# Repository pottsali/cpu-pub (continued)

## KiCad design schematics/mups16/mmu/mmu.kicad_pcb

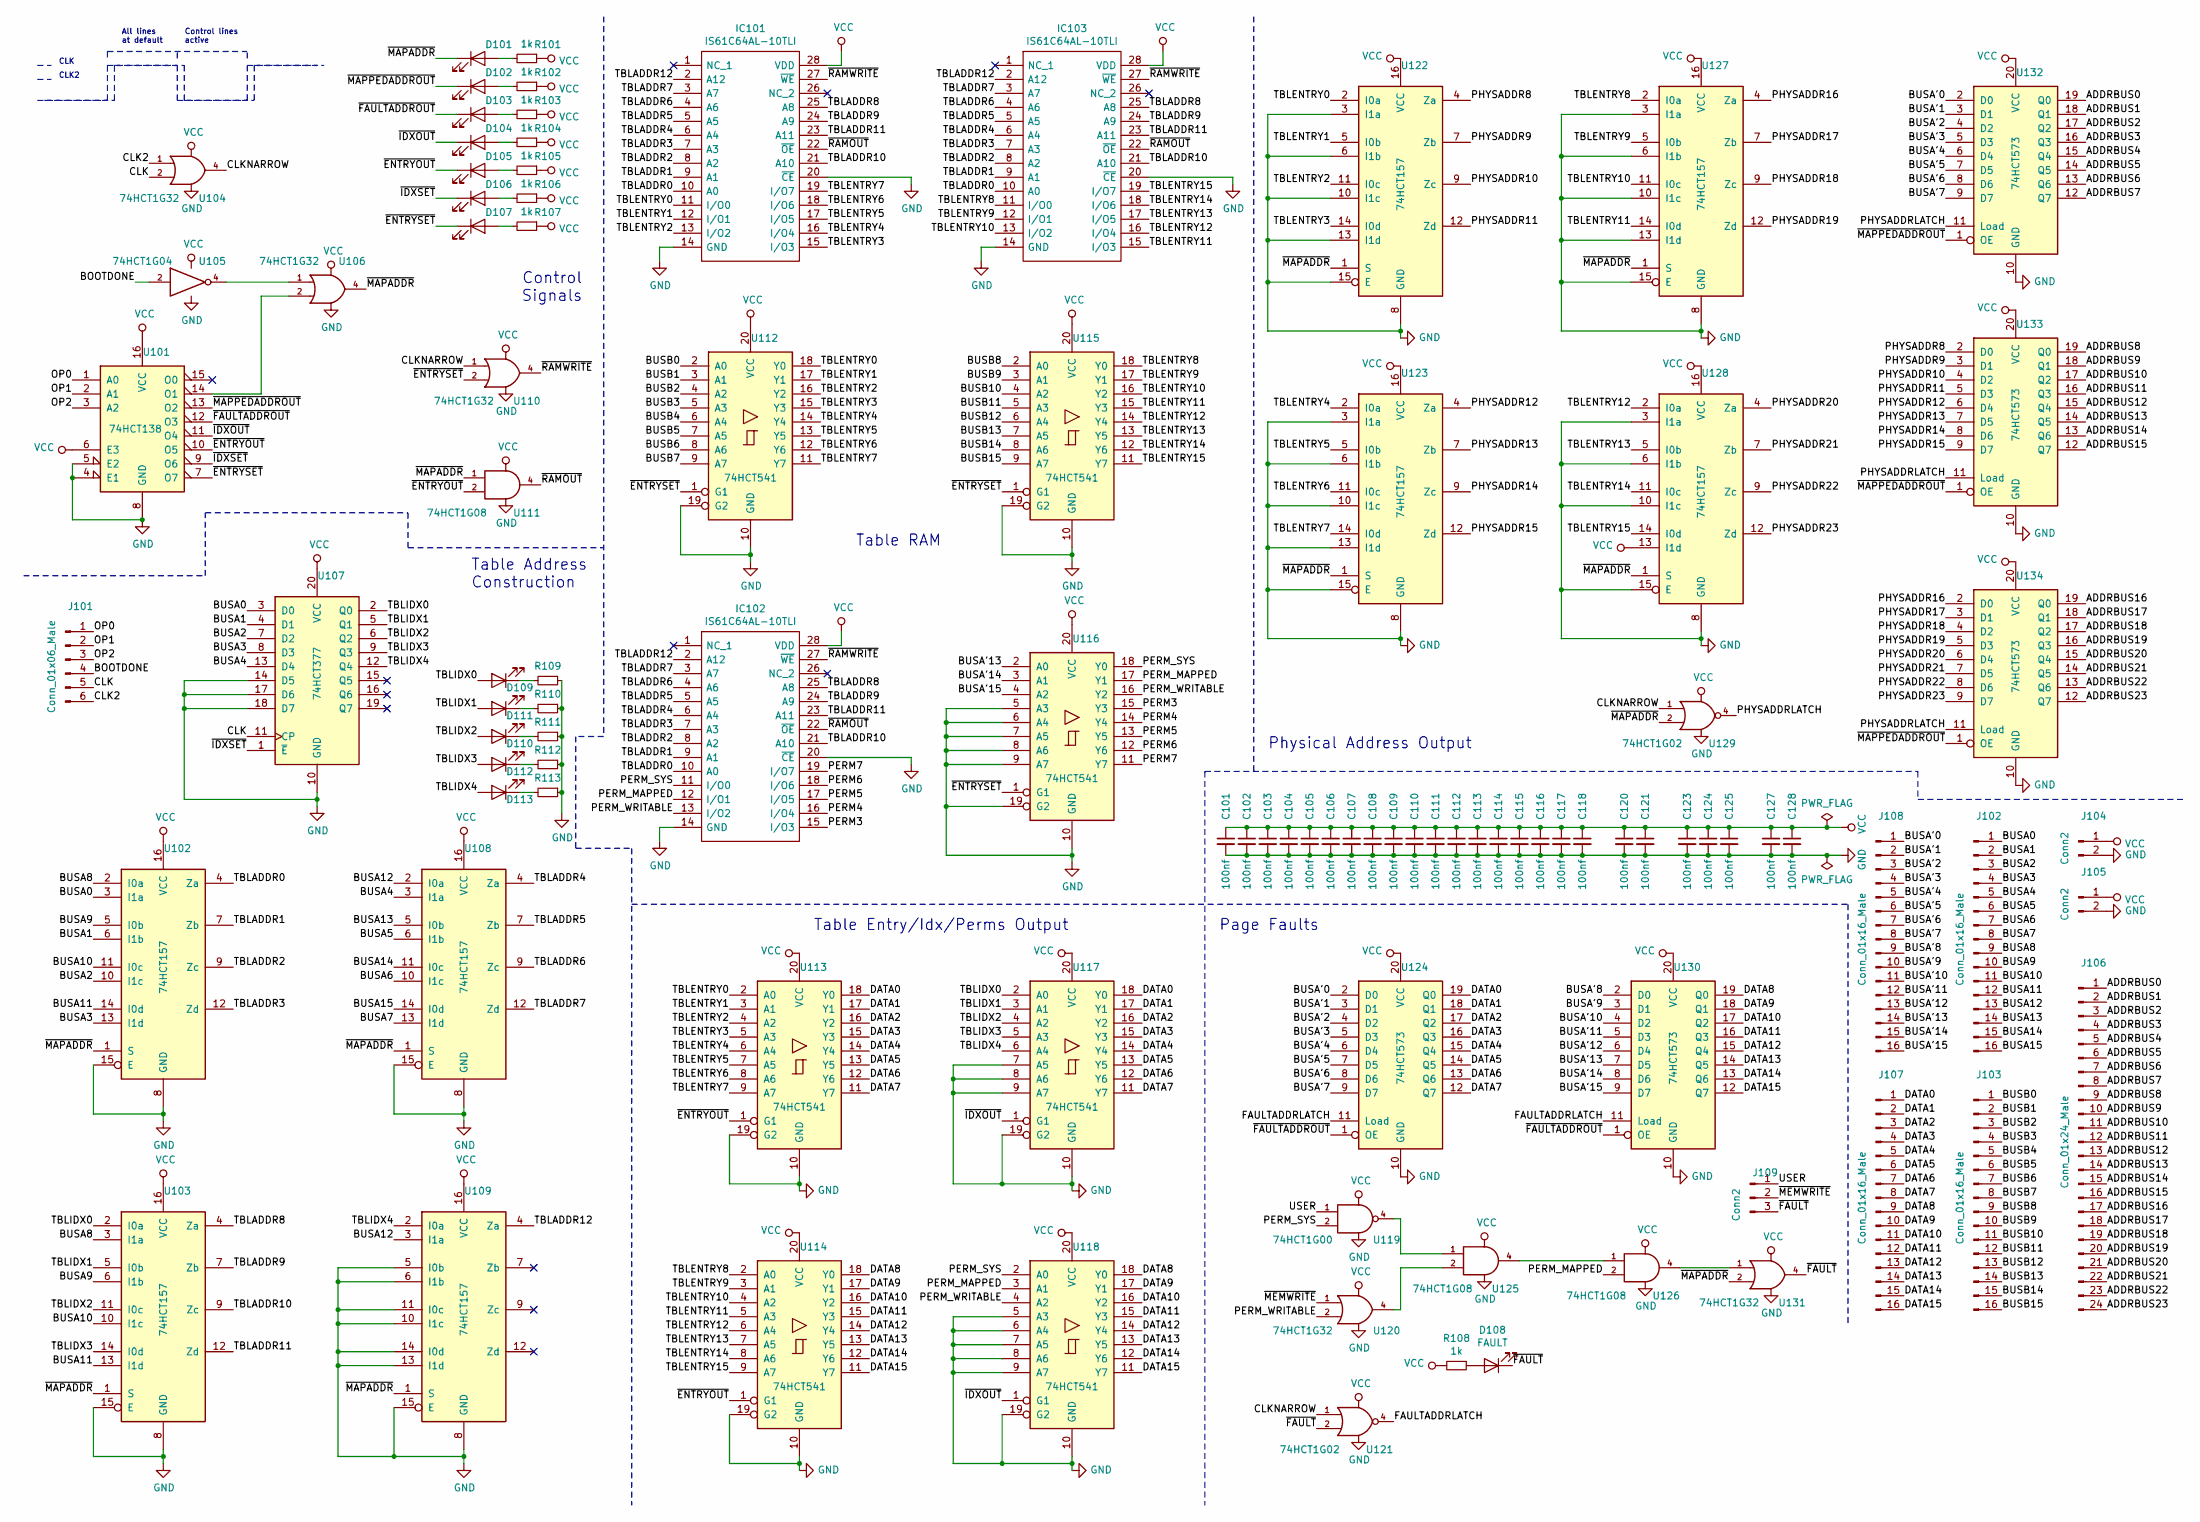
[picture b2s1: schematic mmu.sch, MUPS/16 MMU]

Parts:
C101, C102, C103, C104, C105, C106, C107, C108, C109, C110, C111, C112, C113, C114, C115, C116, C117, C118, C120, C121, C123, C124, C125, C127, C128: 100nf; C_0805_2012Metric
D101: Map Addr; LED_0805_2012Metric
D102: PAddr Out; LED_0805_2012Metric
D103: FAddr Out; LED_0805_2012Metric
D104: TI/P Out; LED_0805_2012Metric
D105: TE Out; LED_0805_2012Metric
D106: TI Set; LED_0805_2012Metric
D107: TE Set; LED_0805_2012Metric
D108: FAULT; LED_0805_2012Metric
D109, D110, D111, D112, D113: LED; LED_0805_2012Metric
IC101, IC102, IC103: IS61C64AL-10TLI; SOP55P1340X120-28N; Mouser Part Number 870-IS61C64AL-10TLI
J101: Conn_01x06_Male; PinHeader_1x06_P2.54mm_Vertical
J102, J103, J107, J108: Conn_01x16_Male; PinHeader_1x16_P2.54mm_Vertical
J104, J105: Conn2; PinHeader_1x02_P2.54mm_Vertical
J106: Conn_01x24_Male; PinHeader_1x24_P2.54mm_Vertical
J109: Conn2; PinHeader_1x03_P2.54mm_Vertical
R101, R102, R103, R104, R105, R106, R107, R108: 1k; R_0805_2012Metric
R109, R110, R111, R112, R113: R_Small; R_0805_2012Metric
U101: 74HCT138; SOIC-16_3.9x9.9mm_P1.27mm
U102, U103, U108, U109, U122, U123, U127, U128: 74HCT157; SOIC-16_3.9x9.9mm_P1.27mm
U104, U106, U110, U120, U131: 74HCT1G32; TSOP-5_1.65x3.05mm_P0.95mm
U105: 74HCT1G04; TSOP-5_1.65x3.05mm_P0.95mm
U107: 74HCT377; SO-20_12.8x7.5mm_P1.27mm
U111, U125, U126: 74HCT1G08; TSOP-5_1.65x3.05mm_P0.95mm
U112, U113, U114, U115, U116, U117, U118: 74HCT541; SOIC-20W_7.5x12.8mm_P1.27mm
U119: 74HCT1G00; TSOP-5_1.65x3.05mm_P0.95mm
U121, U129: 74HCT1G02; SOT65P212X110-5N
U124, U130, U132, U133, U134: 74HCT573; SO-20_12.8x7.5mm_P1.27mm

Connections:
/ADDRBUS0: J106.1, U132.19 (Q0)
/ADDRBUS1: J106.2, U132.18 (Q1)
/ADDRBUS2: J106.3, U132.17 (Q2)
/ADDRBUS3: J106.4, U132.16 (Q3)
/ADDRBUS4: J106.5, U132.15 (Q4)
/ADDRBUS5: J106.6, U132.14 (Q5)
/ADDRBUS6: J106.7, U132.13 (Q6)
/ADDRBUS7: J106.8, U132.12 (Q7)
/ADDRBUS8: J106.9, U133.19 (Q0)
/ADDRBUS9: J106.10, U133.18 (Q1)
/ADDRBUS10: J106.11, U133.17 (Q2)
/ADDRBUS11: J106.12, U133.16 (Q3)
/ADDRBUS12: J106.13, U133.15 (Q4)
/ADDRBUS13: J106.14, U133.14 (Q5)
/ADDRBUS14: J106.15, U133.13 (Q6)
/ADDRBUS15: J106.16, U133.12 (Q7)
/ADDRBUS16: J106.17, U134.19 (Q0)
/ADDRBUS17: J106.18, U134.18 (Q1)
/ADDRBUS18: J106.19, U134.17 (Q2)
/ADDRBUS19: J106.20, U134.16 (Q3)
/ADDRBUS20: J106.21, U134.15 (Q4)
/ADDRBUS21: J106.22, U134.14 (Q5)
/ADDRBUS22: J106.23, U134.13 (Q6)
/ADDRBUS23: J106.24, U134.12 (Q7)
/BOOTDONE: J101.4, U105.2
/BUSA0: J102.1, U102.3 (I1a), U107.3 (D0)
/BUSA1: J102.2, U102.6 (I1b), U107.4 (D1)
/BUSA2: J102.3, U102.10 (I1c), U107.7 (D2)
/BUSA3: J102.4, U102.13 (I1d), U107.8 (D3)
/BUSA4: J102.5, U107.13 (D4), U108.3 (I1a)
/BUSA5: J102.6, U108.6 (I1b)
/BUSA6: J102.7, U108.10 (I1c)
/BUSA7: J102.8, U108.13 (I1d)
/BUSA8: J102.9, U102.2 (I0a), U103.3 (I1a)
/BUSA9: J102.10, U102.5 (I0b), U103.6 (I1b)
/BUSA10: J102.11, U102.11 (I0c), U103.10 (I1c)
/BUSA11: J102.12, U102.14 (I0d), U103.13 (I1d)
/BUSA12: J102.13, U108.2 (I0a), U109.3 (I1a)
/BUSA13: J102.14, U108.5 (I0b)
/BUSA14: J102.15, U108.11 (I0c)
/BUSA15: J102.16, U108.14 (I0d)
/BUSA'0: J108.1, U124.2 (D0), U132.2 (D0)
/BUSA'1: J108.2, U124.3 (D1), U132.3 (D1)
/BUSA'2: J108.3, U124.4 (D2), U132.4 (D2)
/BUSA'3: J108.4, U124.5 (D3), U132.5 (D3)
/BUSA'4: J108.5, U124.6 (D4), U132.6 (D4)
/BUSA'5: J108.6, U124.7 (D5), U132.7 (D5)
/BUSA'6: J108.7, U124.8 (D6), U132.8 (D6)
/BUSA'7: J108.8, U124.9 (D7), U132.9 (D7)
/BUSA'8: J108.9, U130.2 (D0)
/BUSA'9: J108.10, U130.3 (D1)
/BUSA'10: J108.11, U130.4 (D2)
/BUSA'11: J108.12, U130.5 (D3)
/BUSA'12: J108.13, U130.6 (D4)
/BUSA'13: J108.14, U116.2 (A0), U130.7 (D5)
/BUSA'14: J108.15, U116.3 (A1), U130.8 (D6)
/BUSA'15: J108.16, U116.4 (A2), U130.9 (D7)
/BUSB0: J103.1, U112.2 (A0)
/BUSB1: J103.2, U112.3 (A1)
/BUSB2: J103.3, U112.4 (A2)
/BUSB3: J103.4, U112.5 (A3)
/BUSB4: J103.5, U112.6 (A4)
/BUSB5: J103.6, U112.7 (A5)
/BUSB6: J103.7, U112.8 (A6)
/BUSB7: J103.8, U112.9 (A7)
/BUSB8: J103.9, U115.2 (A0)
/BUSB9: J103.10, U115.3 (A1)
/BUSB10: J103.11, U115.4 (A2)
/BUSB11: J103.12, U115.5 (A3)
/BUSB12: J103.13, U115.6 (A4)
/BUSB13: J103.14, U115.7 (A5)
/BUSB14: J103.15, U115.8 (A6)
/BUSB15: J103.16, U115.9 (A7)
/CLK: J101.5, U104.2, U107.11 (CP)
/CLK2: J101.6, U104.1
/CLKNARROW: U104.4, U110.1, U121.1, U129.1
/DATA0: J107.1, U113.18 (Y0), U117.18 (Y0), U124.19 (Q0)
/DATA1: J107.2, U113.17 (Y1), U117.17 (Y1), U124.18 (Q1)
/DATA2: J107.3, U113.16 (Y2), U117.16 (Y2), U124.17 (Q2)
/DATA3: J107.4, U113.15 (Y3), U117.15 (Y3), U124.16 (Q3)
/DATA4: J107.5, U113.14 (Y4), U117.14 (Y4), U124.15 (Q4)
/DATA5: J107.6, U113.13 (Y5), U117.13 (Y5), U124.14 (Q5)
/DATA6: J107.7, U113.12 (Y6), U117.12 (Y6), U124.13 (Q6)
/DATA7: J107.8, U113.11 (Y7), U117.11 (Y7), U124.12 (Q7)
/DATA8: J107.9, U114.18 (Y0), U118.18 (Y0), U130.19 (Q0)
/DATA9: J107.10, U114.17 (Y1), U118.17 (Y1), U130.18 (Q1)
/DATA10: J107.11, U114.16 (Y2), U118.16 (Y2), U130.17 (Q2)
/DATA11: J107.12, U114.15 (Y3), U118.15 (Y3), U130.16 (Q3)
/DATA12: J107.13, U114.14 (Y4), U118.14 (Y4), U130.15 (Q4)
/DATA13: J107.14, U114.13 (Y5), U118.13 (Y5), U130.14 (Q5)
/DATA14: J107.15, U114.12 (Y6), U118.12 (Y6), U130.13 (Q6)
/DATA15: J107.16, U114.11 (Y7), U118.11 (Y7), U130.12 (Q7)
/FAULTADDRLATCH: U121.4, U124.11 (Load), U130.11 (Load)
/OP0: J101.1, U101.1 (A0)
/OP1: J101.2, U101.2 (A1)
/OP2: J101.3, U101.3 (A2)
/PERM3: IC102.15 (I/O3), U116.15 (Y3)
/PERM4: IC102.16 (I/O4), U116.14 (Y4)
/PERM5: IC102.17 (I/O5), U116.13 (Y5)
/PERM6: IC102.18 (I/O6), U116.12 (Y6)
/PERM7: IC102.19 (I/O7), U116.11 (Y7)
/PERM_MAPPED: IC102.12 (I/O1), U116.17 (Y1), U118.3 (A1), U126.2
/PERM_SYS: IC102.11 (I/O0), U116.18 (Y0), U118.2 (A0), U119.2
/PERM_WRITABLE: IC102.13 (I/O2), U116.16 (Y2), U118.4 (A2), U120.2
/PHYSADDR8: U122.4 (Za), U133.2 (D0)
/PHYSADDR9: U122.7 (Zb), U133.3 (D1)
/PHYSADDR10: U122.9 (Zc), U133.4 (D2)
/PHYSADDR11: U122.12 (Zd), U133.5 (D3)
/PHYSADDR12: U123.4 (Za), U133.6 (D4)
/PHYSADDR13: U123.7 (Zb), U133.7 (D5)
/PHYSADDR14: U123.9 (Zc), U133.8 (D6)
/PHYSADDR15: U123.12 (Zd), U133.9 (D7)
/PHYSADDR16: U127.4 (Za), U134.2 (D0)
/PHYSADDR17: U127.7 (Zb), U134.3 (D1)
/PHYSADDR18: U127.9 (Zc), U134.4 (D2)
/PHYSADDR19: U127.12 (Zd), U134.5 (D3)
/PHYSADDR20: U128.4 (Za), U134.6 (D4)
/PHYSADDR21: U128.7 (Zb), U134.7 (D5)
/PHYSADDR22: U128.9 (Zc), U134.8 (D6)
/PHYSADDR23: U128.12 (Zd), U134.9 (D7)
/PHYSADDRLATCH: U129.4, U132.11 (Load), U133.11 (Load), U134.11 (Load)
/TBLADDR0: IC101.10 (A0), IC102.10 (A0), IC103.10 (A0), U102.4 (Za)
/TBLADDR1: IC101.9 (A1), IC102.9 (A1), IC103.9 (A1), U102.7 (Zb)
/TBLADDR2: IC101.8 (A2), IC102.8 (A2), IC103.8 (A2), U102.9 (Zc)
/TBLADDR3: IC101.7 (A3), IC102.7 (A3), IC103.7 (A3), U102.12 (Zd)
/TBLADDR4: IC101.6 (A4), IC102.6 (A4), IC103.6 (A4), U108.4 (Za)
/TBLADDR5: IC101.5 (A5), IC102.5 (A5), IC103.5 (A5), U108.7 (Zb)
/TBLADDR6: IC101.4 (A6), IC102.4 (A6), IC103.4 (A6), U108.9 (Zc)
/TBLADDR7: IC101.3 (A7), IC102.3 (A7), IC103.3 (A7), U108.12 (Zd)
/TBLADDR8: IC101.25 (A8), IC102.25 (A8), IC103.25 (A8), U103.4 (Za)
/TBLADDR9: IC101.24 (A9), IC102.24 (A9), IC103.24 (A9), U103.7 (Zb)
/TBLADDR10: IC101.21 (A10), IC102.21 (A10), IC103.21 (A10), U103.9 (Zc)
/TBLADDR11: IC101.23 (A11), IC102.23 (A11), IC103.23 (A11), U103.12 (Zd)
/TBLADDR12: IC101.2 (A12), IC102.2 (A12), IC103.2 (A12), U109.4 (Za)
/TBLENTRY0: IC101.11 (I/O0), U112.18 (Y0), U113.2 (A0), U122.2 (I0a)
/TBLENTRY1: IC101.12 (I/O1), U112.17 (Y1), U113.3 (A1), U122.5 (I0b)
/TBLENTRY2: IC101.13 (I/O2), U112.16 (Y2), U113.4 (A2), U122.11 (I0c)
/TBLENTRY3: IC101.15 (I/O3), U112.15 (Y3), U113.5 (A3), U122.14 (I0d)
/TBLENTRY4: IC101.16 (I/O4), U112.14 (Y4), U113.6 (A4), U123.2 (I0a)
/TBLENTRY5: IC101.17 (I/O5), U112.13 (Y5), U113.7 (A5), U123.5 (I0b)
/TBLENTRY6: IC101.18 (I/O6), U112.12 (Y6), U113.8 (A6), U123.11 (I0c)
/TBLENTRY7: IC101.19 (I/O7), U112.11 (Y7), U113.9 (A7), U123.14 (I0d)
/TBLENTRY8: IC103.11 (I/O0), U114.2 (A0), U115.18 (Y0), U127.2 (I0a)
/TBLENTRY9: IC103.12 (I/O1), U114.3 (A1), U115.17 (Y1), U127.5 (I0b)
/TBLENTRY10: IC103.13 (I/O2), U114.4 (A2), U115.16 (Y2), U127.11 (I0c)
/TBLENTRY11: IC103.15 (I/O3), U114.5 (A3), U115.15 (Y3), U127.14 (I0d)
/TBLENTRY12: IC103.16 (I/O4), U114.6 (A4), U115.14 (Y4), U128.2 (I0a)
/TBLENTRY13: IC103.17 (I/O5), U114.7 (A5), U115.13 (Y5), U128.5 (I0b)
/TBLENTRY14: IC103.18 (I/O6), U114.8 (A6), U115.12 (Y6), U128.11 (I0c)
/TBLENTRY15: IC103.19 (I/O7), U114.9 (A7), U115.11 (Y7), U128.14 (I0d)
/TBLIDX0: D109.2 (A), U103.2 (I0a), U107.2 (Q0), U117.2 (A0)
/TBLIDX1: D110.2 (A), U103.5 (I0b), U107.5 (Q1), U117.3 (A1)
/TBLIDX2: D111.2 (A), U103.11 (I0c), U107.6 (Q2), U117.4 (A2)
/TBLIDX3: D112.2 (A), U103.14 (I0d), U107.9 (Q3), U117.5 (A3)
/TBLIDX4: D113.2 (A), U107.12 (Q4), U109.2 (I0a), U117.6 (A4)
/USER: J109.1, U119.1
/~ENTRYOUT: D105.1 (K), U101.10 (O5), U111.2, U113.1 (G1), U114.1 (G1)
/~ENTRYSET: D107.1 (K), U101.7 (O7), U110.2, U112.1 (G1), U115.1 (G1), U116.1 (G1)
/~FAULT: D108.1 (K), J109.3, U121.2, U131.4
/~FAULTADDROUT: D103.1 (K), U101.12 (O3), U124.1 (OE), U130.1 (OE)
/~IDXOUT: D104.1 (K), U101.11 (O4), U117.1 (G1), U118.1 (G1)
/~IDXSET: D106.1 (K), U101.9 (O6), U107.1 (~E)
/~MAPADDR: D101.1 (K), U102.1 (S), U103.1 (S), U106.4, U108.1 (S), U109.1 (S), U111.1, U122.1 (S), U123.1 (S), U127.1 (S), U128.1 (S), U129.2, U131.2
/~MAPPEDADDROUT: D102.1 (K), U101.13 (O2), U132.1 (OE), U133.1 (OE), U134.1 (OE)
/~MEMWRITE: J109.2, U120.1
/~RAMOUT: IC101.22 (~OE), IC102.22 (~OE), IC103.22 (~OE), U111.4
/~RAMWRITE: IC101.27 (~WE), IC102.27 (~WE), IC103.27 (~WE), U110.4
GND: C101.2, C102.2, C103.2, C104.2, C105.2, C106.2, C107.2, C108.2, C109.2, C110.2, C111.2, C112.2, C113.2, C114.2, C115.2, C116.2, C117.2, C118.2, C120.2, C121.2, C123.2, C124.2, C125.2, C127.2, C128.2, IC101.14 (GND), IC101.20 (~CE), IC102.14 (GND), IC102.20 (~CE), IC103.14 (GND), IC103.20 (~CE), J104.2, J105.2, R109.1, R110.1, R111.1, R112.1, R113.1, U101.4 (E1), U101.5 (E2), U101.8 (GND), U102.8 (GND), U102.15 (E), U103.8 (GND), U103.15 (E), U104.3 (GND), U105.3 (GND), U106.3 (GND), U107.10 (GND), U107.14 (D5), U107.17 (D6), U107.18 (D7), U108.8 (GND), U108.15 (E), U109.5 (I0b), U109.6 (I1b), U109.8 (GND), U109.10 (I1c), U109.11 (I0c), U109.13 (I1d), U109.14 (I0d), U109.15 (E), U110.3 (GND), U111.3 (GND), U112.10 (GND), U112.19 (G2), U113.10 (GND), U113.19 (G2), U114.10 (GND), U114.19 (G2), U115.10 (GND), U115.19 (G2), U116.5 (A3), U116.6 (A4), U116.7 (A5), U116.8 (A6), U116.9 (A7), U116.10 (GND), U116.19 (G2), U117.7 (A5), U117.8 (A6), U117.9 (A7), U117.10 (GND), U117.19 (G2), U118.5 (A3), U118.6 (A4), U118.7 (A5), U118.8 (A6), U118.9 (A7), U118.10 (GND), U118.19 (G2), U119.3 (GND), U120.3 (GND), U121.3 (GND), U122.3 (I1a), U122.6 (I1b), U122.8 (GND), U122.10 (I1c), U122.13 (I1d), U122.15 (E), U123.3 (I1a), U123.6 (I1b), U123.8 (GND), U123.10 (I1c), U123.13 (I1d), U123.15 (E), U124.10 (GND), U125.3 (GND), U126.3 (GND), U127.3 (I1a), U127.6 (I1b), U127.8 (GND), U127.10 (I1c), U127.13 (I1d), U127.15 (E), U128.3 (I1a), U128.6 (I1b), U128.8 (GND), U128.10 (I1c), U128.15 (E), U129.3 (GND), U130.10 (GND), U131.3 (GND), U132.10 (GND), U133.10 (GND), U134.10 (GND)
unnamed: D101.2 (A), R101.2
unnamed: D102.2 (A), R102.2
unnamed: D103.2 (A), R103.2
unnamed: D104.2 (A), R104.2
unnamed: D105.2 (A), R105.2
unnamed: D106.2 (A), R106.2
unnamed: D107.2 (A), R107.2
unnamed: D108.2 (A), R108.1
unnamed: D109.1 (K), R109.2
unnamed: D110.1 (K), R110.2
unnamed: D111.1 (K), R111.2
unnamed: D112.1 (K), R112.2
unnamed: D113.1 (K), R113.2
unnamed: U101.14 (O1), U106.2
unnamed: U105.4, U106.1
unnamed: U119.4, U125.1
unnamed: U120.4, U125.2
unnamed: U125.4, U126.1
unnamed: U126.4, U131.1
VCC: C101.1, C102.1, C103.1, C104.1, C105.1, C106.1, C107.1, C108.1, C109.1, C110.1, C111.1, C112.1, C113.1, C114.1, C115.1, C116.1, C117.1, C118.1, C120.1, C121.1, C123.1, C124.1, C125.1, C127.1, C128.1, IC101.28 (VDD), IC102.28 (VDD), IC103.28 (VDD), J104.1, J105.1, R101.1, R102.1, R103.1, R104.1, R105.1, R106.1, R107.1, R108.2, U101.6 (E3), U101.16 (VCC), U102.16 (VCC), U103.16 (VCC), U104.5 (VCC), U105.5 (VCC), U106.5 (VCC), U107.20 (VCC), U108.16 (VCC), U109.16 (VCC), U110.5 (VCC), U111.5 (VCC), U112.20 (VCC), U113.20 (VCC), U114.20 (VCC), U115.20 (VCC), U116.20 (VCC), U117.20 (VCC), U118.20 (VCC), U119.5 (VCC), U120.5 (VCC), U121.5 (VCC), U122.16 (VCC), U123.16 (VCC), U124.20 (VCC), U125.5 (VCC), U126.5 (VCC), U127.16 (VCC), U128.13 (I1d), U128.16 (VCC), U129.5 (VCC), U130.20 (VCC), U131.5 (VCC), U132.20 (VCC), U133.20 (VCC), U134.20 (VCC)

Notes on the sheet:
All lines at default
Control lines active
CLK
CLK2
Table Address Construction
Control Signals
Table RAM
Table Entry/Idx/Perms Output
Physical Address Output
Page Faults

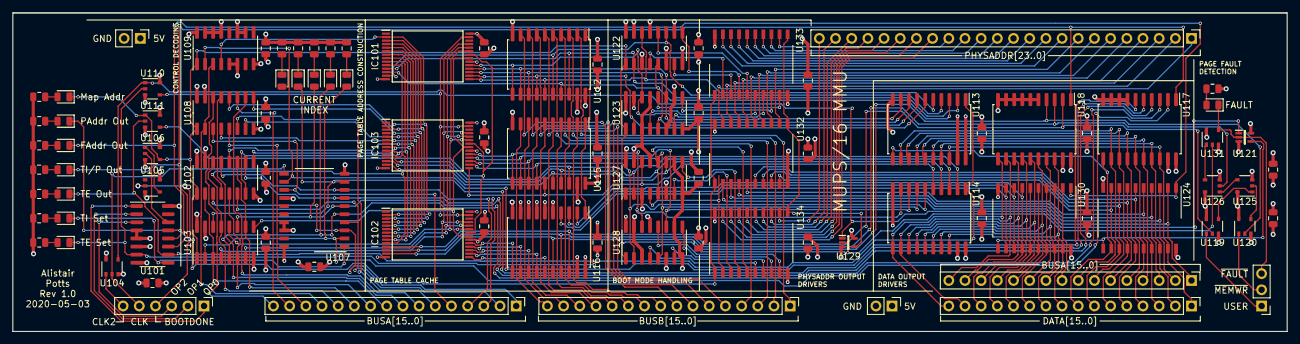
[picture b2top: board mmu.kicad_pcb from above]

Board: 4 copper layers, 200.0 x 50.0 mm, 97 parts (0 on the bottom side), 188 nets.

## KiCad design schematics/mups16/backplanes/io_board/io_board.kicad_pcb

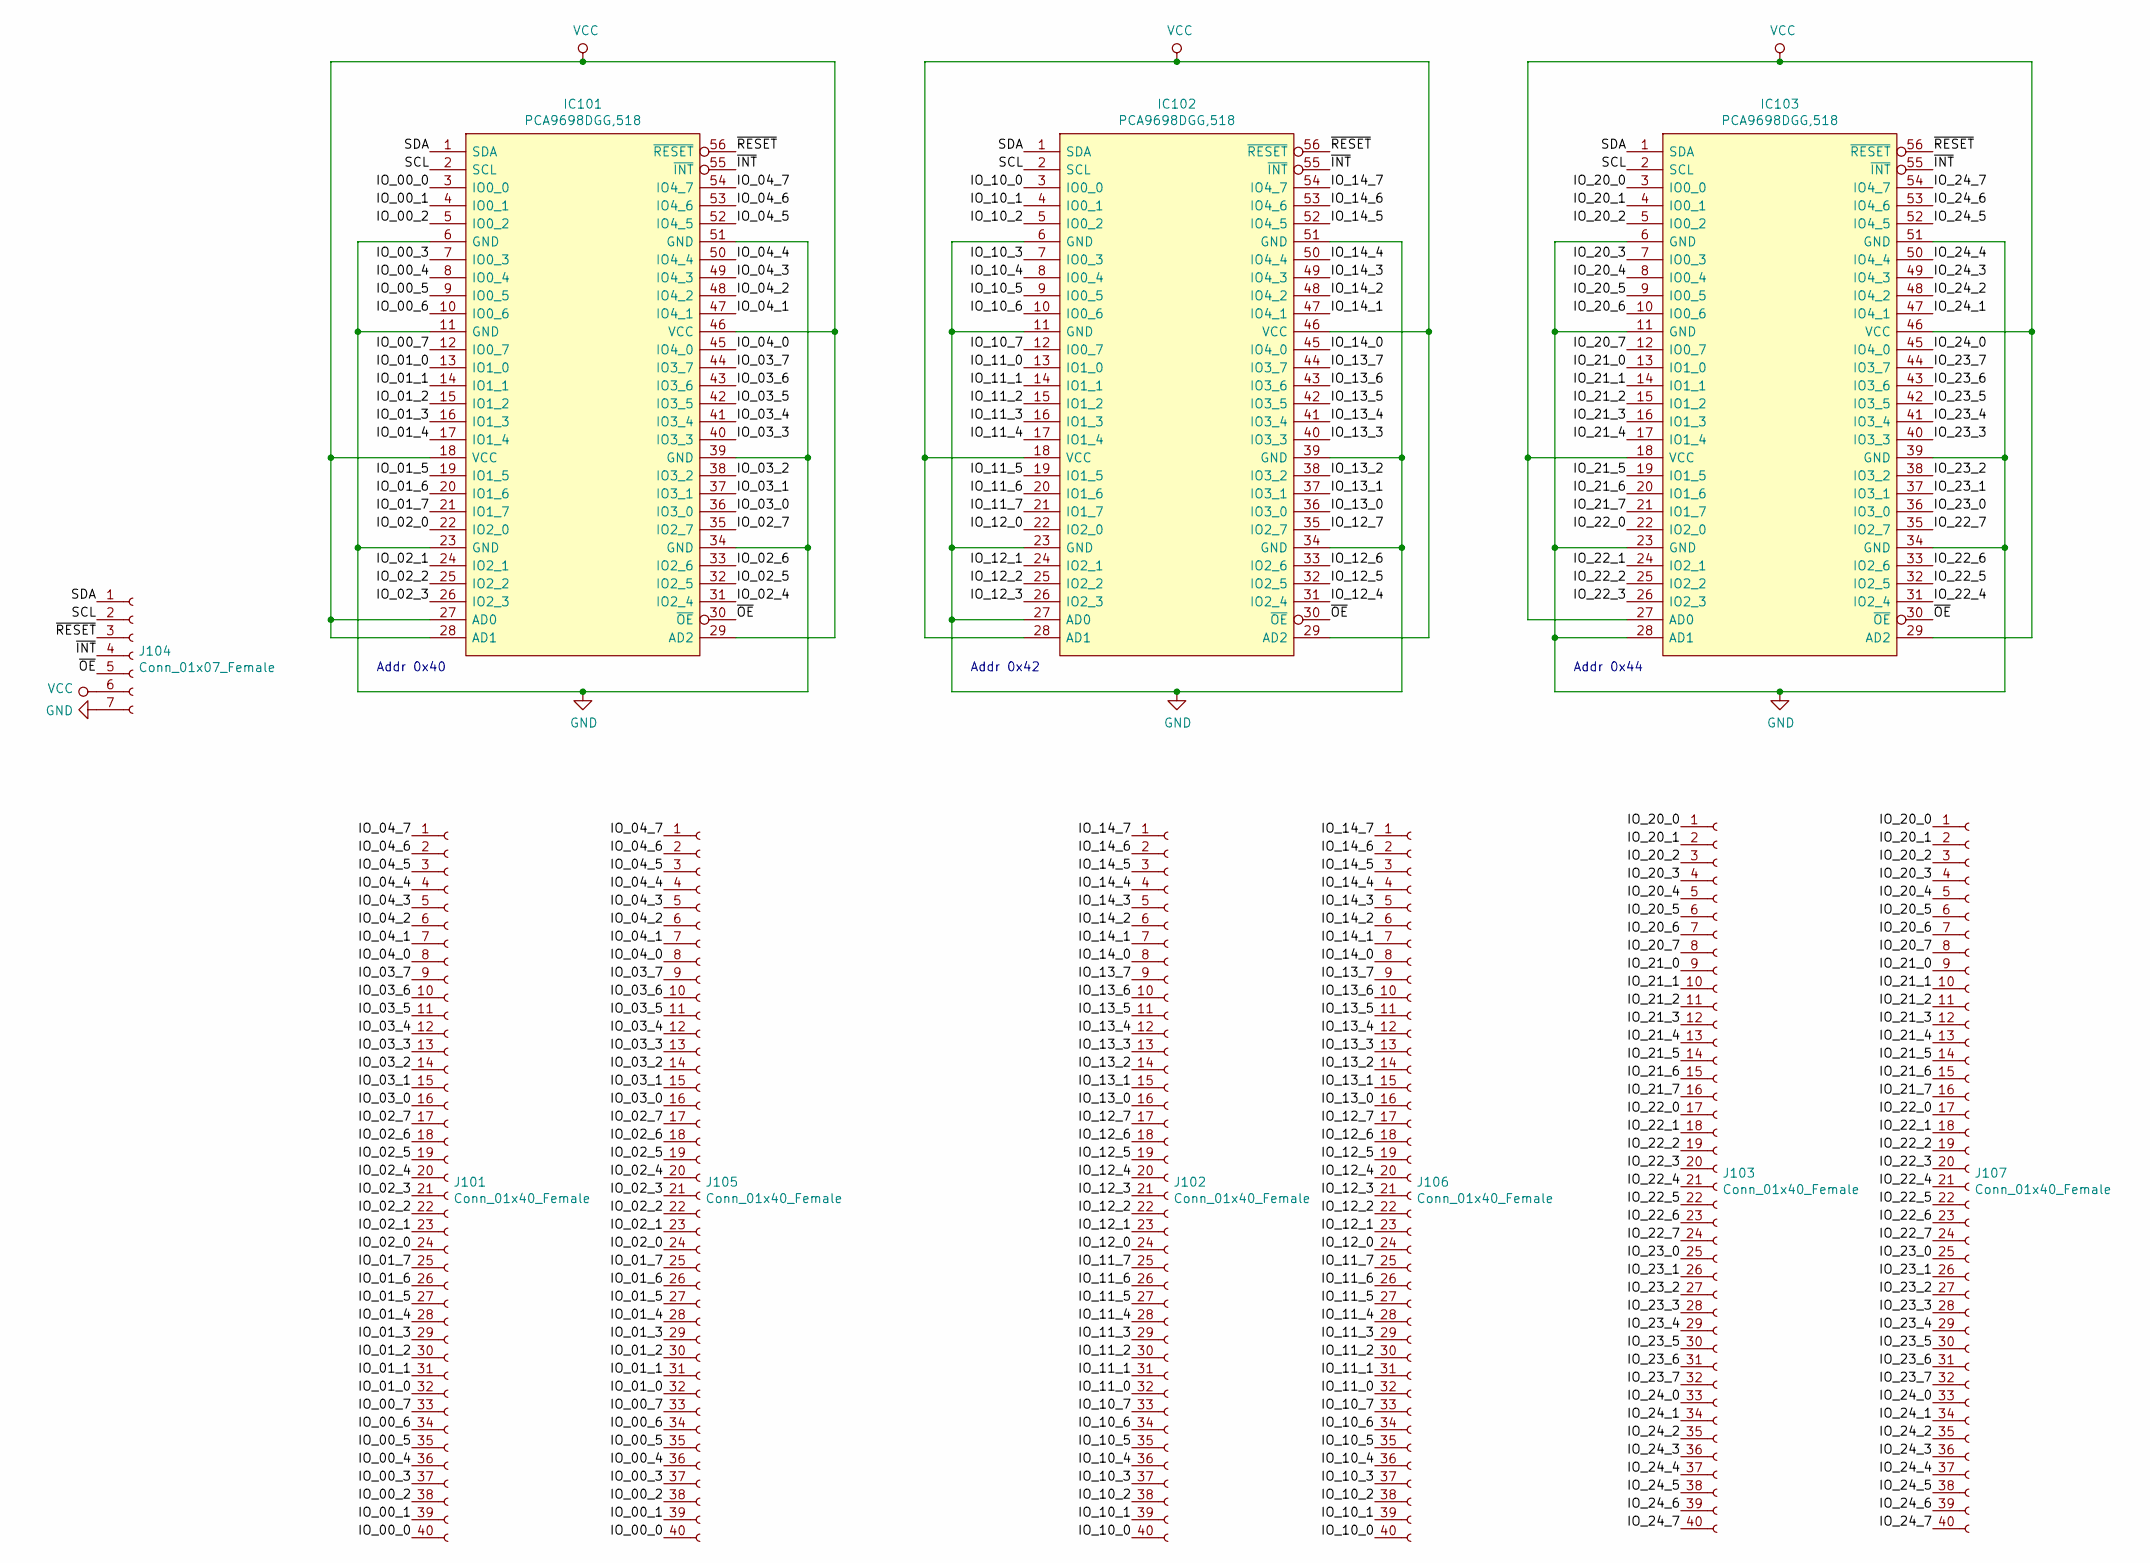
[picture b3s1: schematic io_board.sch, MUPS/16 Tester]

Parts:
IC101, IC102, IC103: PCA9698DGG,518; SOP50P810X120-56N; Mouser Part Number 771-PCA9698DGG-T
J101, J102, J103, J105, J106, J107: Conn_01x40_Female; PinSocket_2x20_P2.54mm_Vertical
J104: Conn_01x07_Female; PinSocket_1x07_P2.54mm_Vertical

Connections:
/IO_00_0: IC101.3 (IO0_0), J101.40, J105.40
/IO_00_1: IC101.4 (IO0_1), J101.39, J105.39
/IO_00_2: IC101.5 (IO0_2), J101.38, J105.38
/IO_00_3: IC101.7 (IO0_3), J101.37, J105.37
/IO_00_4: IC101.8 (IO0_4), J101.36, J105.36
/IO_00_5: IC101.9 (IO0_5), J101.35, J105.35
/IO_00_6: IC101.10 (IO0_6), J101.34, J105.34
/IO_00_7: IC101.12 (IO0_7), J101.33, J105.33
/IO_01_0: IC101.13 (IO1_0), J101.32, J105.32
/IO_01_1: IC101.14 (IO1_1), J101.31, J105.31
/IO_01_2: IC101.15 (IO1_2), J101.30, J105.30
/IO_01_3: IC101.16 (IO1_3), J101.29, J105.29
/IO_01_4: IC101.17 (IO1_4), J101.28, J105.28
/IO_01_5: IC101.19 (IO1_5), J101.27, J105.27
/IO_01_6: IC101.20 (IO1_6), J101.26, J105.26
/IO_01_7: IC101.21 (IO1_7), J101.25, J105.25
/IO_02_0: IC101.22 (IO2_0), J101.24, J105.24
/IO_02_1: IC101.24 (IO2_1), J101.23, J105.23
/IO_02_2: IC101.25 (IO2_2), J101.22, J105.22
/IO_02_3: IC101.26 (IO2_3), J101.21, J105.21
/IO_02_4: IC101.31 (IO2_4), J101.20, J105.20
/IO_02_5: IC101.32 (IO2_5), J101.19, J105.19
/IO_02_6: IC101.33 (IO2_6), J101.18, J105.18
/IO_02_7: IC101.35 (IO2_7), J101.17, J105.17
/IO_03_0: IC101.36 (IO3_0), J101.16, J105.16
/IO_03_1: IC101.37 (IO3_1), J101.15, J105.15
/IO_03_2: IC101.38 (IO3_2), J101.14, J105.14
/IO_03_3: IC101.40 (IO3_3), J101.13, J105.13
/IO_03_4: IC101.41 (IO3_4), J101.12, J105.12
/IO_03_5: IC101.42 (IO3_5), J101.11, J105.11
/IO_03_6: IC101.43 (IO3_6), J101.10, J105.10
/IO_03_7: IC101.44 (IO3_7), J101.9, J105.9
/IO_04_0: IC101.45 (IO4_0), J101.8, J105.8
/IO_04_1: IC101.47 (IO4_1), J101.7, J105.7
/IO_04_2: IC101.48 (IO4_2), J101.6, J105.6
/IO_04_3: IC101.49 (IO4_3), J101.5, J105.5
/IO_04_4: IC101.50 (IO4_4), J101.4, J105.4
/IO_04_5: IC101.52 (IO4_5), J101.3, J105.3
/IO_04_6: IC101.53 (IO4_6), J101.2, J105.2
/IO_04_7: IC101.54 (IO4_7), J101.1, J105.1
/IO_10_0: IC102.3 (IO0_0), J102.40, J106.40
/IO_10_1: IC102.4 (IO0_1), J102.39, J106.39
/IO_10_2: IC102.5 (IO0_2), J102.38, J106.38
/IO_10_3: IC102.7 (IO0_3), J102.37, J106.37
/IO_10_4: IC102.8 (IO0_4), J102.36, J106.36
/IO_10_5: IC102.9 (IO0_5), J102.35, J106.35
/IO_10_6: IC102.10 (IO0_6), J102.34, J106.34
/IO_10_7: IC102.12 (IO0_7), J102.33, J106.33
/IO_11_0: IC102.13 (IO1_0), J102.32, J106.32
/IO_11_1: IC102.14 (IO1_1), J102.31, J106.31
/IO_11_2: IC102.15 (IO1_2), J102.30, J106.30
/IO_11_3: IC102.16 (IO1_3), J102.29, J106.29
/IO_11_4: IC102.17 (IO1_4), J102.28, J106.28
/IO_11_5: IC102.19 (IO1_5), J102.27, J106.27
/IO_11_6: IC102.20 (IO1_6), J102.26, J106.26
/IO_11_7: IC102.21 (IO1_7), J102.25, J106.25
/IO_12_0: IC102.22 (IO2_0), J102.24, J106.24
/IO_12_1: IC102.24 (IO2_1), J102.23, J106.23
/IO_12_2: IC102.25 (IO2_2), J102.22, J106.22
/IO_12_3: IC102.26 (IO2_3), J102.21, J106.21
/IO_12_4: IC102.31 (IO2_4), J102.20, J106.20
/IO_12_5: IC102.32 (IO2_5), J102.19, J106.19
/IO_12_6: IC102.33 (IO2_6), J102.18, J106.18
/IO_12_7: IC102.35 (IO2_7), J102.17, J106.17
/IO_13_0: IC102.36 (IO3_0), J102.16, J106.16
/IO_13_1: IC102.37 (IO3_1), J102.15, J106.15
/IO_13_2: IC102.38 (IO3_2), J102.14, J106.14
/IO_13_3: IC102.40 (IO3_3), J102.13, J106.13
/IO_13_4: IC102.41 (IO3_4), J102.12, J106.12
/IO_13_5: IC102.42 (IO3_5), J102.11, J106.11
/IO_13_6: IC102.43 (IO3_6), J102.10, J106.10
/IO_13_7: IC102.44 (IO3_7), J102.9, J106.9
/IO_14_0: IC102.45 (IO4_0), J102.8, J106.8
/IO_14_1: IC102.47 (IO4_1), J102.7, J106.7
/IO_14_2: IC102.48 (IO4_2), J102.6, J106.6
/IO_14_3: IC102.49 (IO4_3), J102.5, J106.5
/IO_14_4: IC102.50 (IO4_4), J102.4, J106.4
/IO_14_5: IC102.52 (IO4_5), J102.3, J106.3
/IO_14_6: IC102.53 (IO4_6), J102.2, J106.2
/IO_14_7: IC102.54 (IO4_7), J102.1, J106.1
/IO_20_0: IC103.3 (IO0_0), J103.1, J107.1
/IO_20_1: IC103.4 (IO0_1), J103.2, J107.2
/IO_20_2: IC103.5 (IO0_2), J103.3, J107.3
/IO_20_3: IC103.7 (IO0_3), J103.4, J107.4
/IO_20_4: IC103.8 (IO0_4), J103.5, J107.5
/IO_20_5: IC103.9 (IO0_5), J103.6, J107.6
/IO_20_6: IC103.10 (IO0_6), J103.7, J107.7
/IO_20_7: IC103.12 (IO0_7), J103.8, J107.8
/IO_21_0: IC103.13 (IO1_0), J103.9, J107.9
/IO_21_1: IC103.14 (IO1_1), J103.10, J107.10
/IO_21_2: IC103.15 (IO1_2), J103.11, J107.11
/IO_21_3: IC103.16 (IO1_3), J103.12, J107.12
/IO_21_4: IC103.17 (IO1_4), J103.13, J107.13
/IO_21_5: IC103.19 (IO1_5), J103.14, J107.14
/IO_21_6: IC103.20 (IO1_6), J103.15, J107.15
/IO_21_7: IC103.21 (IO1_7), J103.16, J107.16
/IO_22_0: IC103.22 (IO2_0), J103.17, J107.17
/IO_22_1: IC103.24 (IO2_1), J103.18, J107.18
/IO_22_2: IC103.25 (IO2_2), J103.19, J107.19
/IO_22_3: IC103.26 (IO2_3), J103.20, J107.20
/IO_22_4: IC103.31 (IO2_4), J103.21, J107.21
/IO_22_5: IC103.32 (IO2_5), J103.22, J107.22
/IO_22_6: IC103.33 (IO2_6), J103.23, J107.23
/IO_22_7: IC103.35 (IO2_7), J103.24, J107.24
/IO_23_0: IC103.36 (IO3_0), J103.25, J107.25
/IO_23_1: IC103.37 (IO3_1), J103.26, J107.26
/IO_23_2: IC103.38 (IO3_2), J103.27, J107.27
/IO_23_3: IC103.40 (IO3_3), J103.28, J107.28
/IO_23_4: IC103.41 (IO3_4), J103.29, J107.29
/IO_23_5: IC103.42 (IO3_5), J103.30, J107.30
/IO_23_6: IC103.43 (IO3_6), J103.31, J107.31
/IO_23_7: IC103.44 (IO3_7), J103.32, J107.32
/IO_24_0: IC103.45 (IO4_0), J103.33, J107.33
/IO_24_1: IC103.47 (IO4_1), J103.34, J107.34
/IO_24_2: IC103.48 (IO4_2), J103.35, J107.35
/IO_24_3: IC103.49 (IO4_3), J103.36, J107.36
/IO_24_4: IC103.50 (IO4_4), J103.37, J107.37
/IO_24_5: IC103.52 (IO4_5), J103.38, J107.38
/IO_24_6: IC103.53 (IO4_6), J103.39, J107.39
/IO_24_7: IC103.54 (IO4_7), J103.40, J107.40
/SCL: IC101.2 (SCL), IC102.2 (SCL), IC103.2 (SCL), J104.2
/SDA: IC101.1 (SDA), IC102.1 (SDA), IC103.1 (SDA), J104.1
/~INT: IC101.55 (~INT), IC102.55 (~INT), IC103.55 (~INT), J104.4
/~OE: IC101.30 (~OE), IC102.30 (~OE), IC103.30 (~OE), J104.5
/~RESET: IC101.56 (~RESET), IC102.56 (~RESET), IC103.56 (~RESET), J104.3
GND: IC101.6 (GND), IC101.11 (GND), IC101.23 (GND), IC101.34 (GND), IC101.39 (GND), IC101.51 (GND), IC102.6 (GND), IC102.11 (GND), IC102.23 (GND), IC102.27 (AD0), IC102.34 (GND), IC102.39 (GND), IC102.51 (GND), IC103.6 (GND), IC103.11 (GND), IC103.23 (GND), IC103.28 (AD1), IC103.34 (GND), IC103.39 (GND), IC103.51 (GND), J104.7
VCC: IC101.18 (VCC), IC101.27 (AD0), IC101.28 (AD1), IC101.29 (AD2), IC101.46 (VCC), IC102.18 (VCC), IC102.28 (AD1), IC102.29 (AD2), IC102.46 (VCC), IC103.18 (VCC), IC103.27 (AD0), IC103.29 (AD2), IC103.46 (VCC), J104.6

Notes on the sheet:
Addr 0x40
Addr 0x42
Addr 0x44

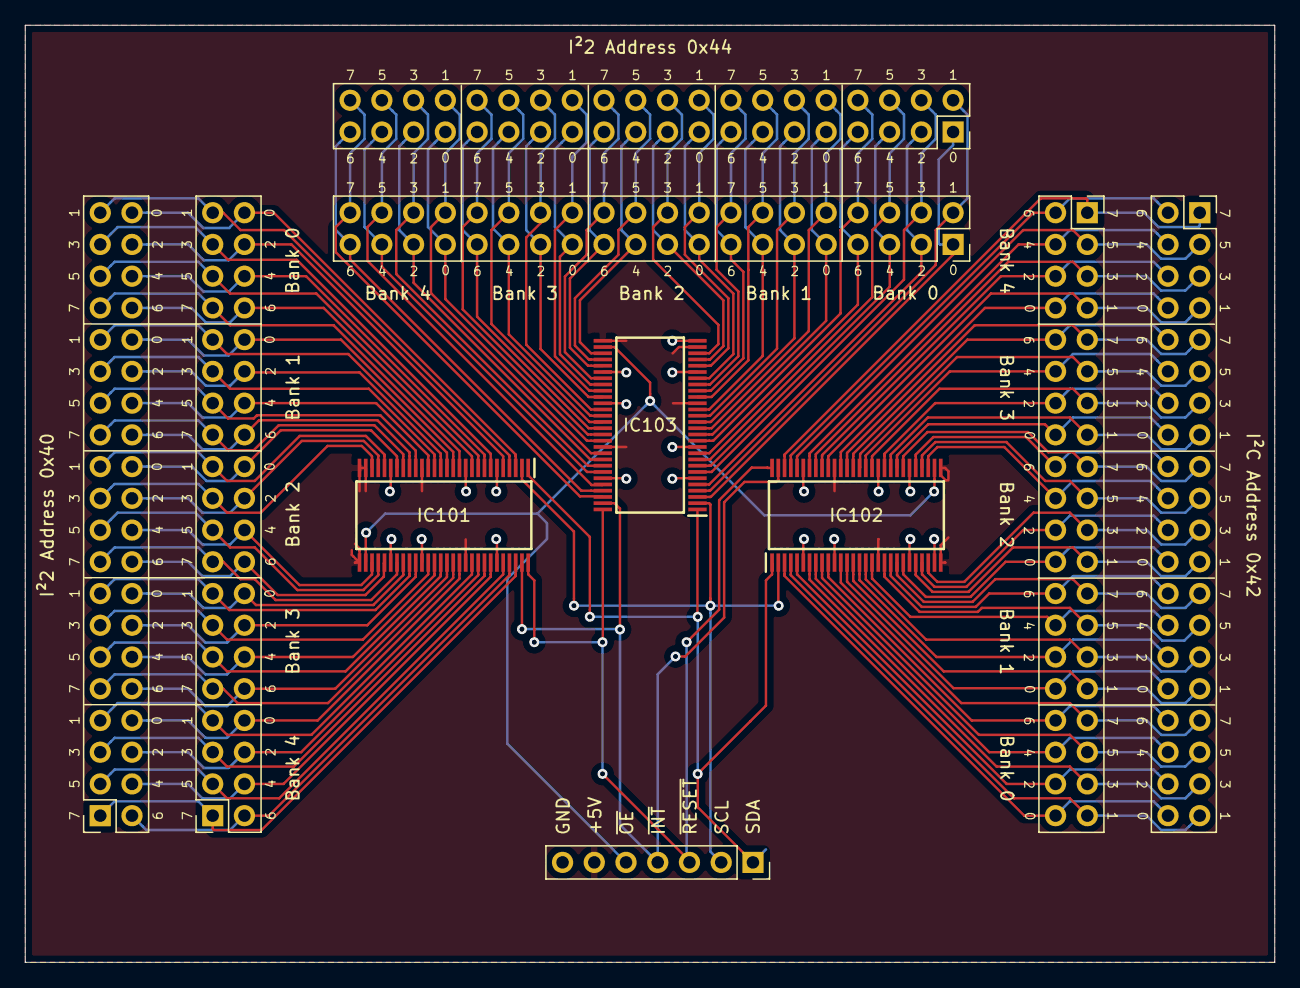
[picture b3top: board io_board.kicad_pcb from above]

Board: 2 copper layers, 100.0 x 75.0 mm, 10 parts (0 on the bottom side), 127 nets.
